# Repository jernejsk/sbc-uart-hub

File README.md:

# SBC UART hub (rev A)

A 16-channel 3.3 V debug-UART adapter for the SBC farm, connected over one USB cable.

```
USB-C ── USBLC6 ── USB2514B hub ──┬── FT4232HL #1  CH01-04 (top row, left)
                                  ├── FT4232HL #2  CH05-08 (top row, right)
                                  ├── FT4232HL #3  CH09-12 (bottom row, left)
                                  └── FT4232HL #4  CH13-16 (bottom row, right)
```

The datasheet with 3D renders, for design review, is at `docs/datasheet.html` (images in `docs/img/`).

Each channel works as follows:

- The FT TXD goes through a 74LVC125 buffer, then 220R, to the header. The buffer's /OE is that channel's DTR#.
- The connector RX comes in through 220R and the 74LVC125 (always enabled) to the FT RXD.
- The ESDA6V1-5SC6 clamps the connector pins to GND only. It has no VCC rail.
- A green LED lights while DTR is asserted, which means the port is open and TX is driven.

TX is Hi-Z whenever the port is closed. LVC parts have Ioff, so both TX and RX are also Hi-Z when the board is unpowered. As a result the DUT is never back-powered, and the cable carries no VCC.

## Connector (1x3 2.54 mm right-angle header, LCSC C492411)

| pin | signal | direction |
|-----|--------|-----------|
| 1 (square) | GND | |
| 2 | TX | adapter → DUT RX |
| 3 | RX | DUT TX → adapter |

Each header's plastic body is flush with the board edge, and its pins stick out about 6 mm past it. Pin 1 (GND, square pad) is on the right in the top row (CH01-08) and on the left in the bottom row (CH09-16). GND, TX and RX are printed next to every pin.

The project footprint (`gen/mkfp.py`, `hw/lib/sbcu.pretty`) numbers its pads the mirror of KiCad's stock right-angle header. That puts each signal where it was on the earlier JST-XH layout (commit 3d51c3360c3e), so that routing was kept; the header itself is symmetric. `gen/rework_headers.py` did the migration: it swapped the footprints, ripped only the connector stubs and locked the rest. It then had Freerouting finish the stubs. A fresh `build_pcb.py` + `route.py` run gives the same placement but a different autorouted result.

Cables are plain female-female Dupont jumper wires, one per signal, so any DUT header order works. Plugging one onto the wrong pin is harmless: there is no VCC pin, and both lines have 220R in series behind an LVC buffer.

The back silkscreen has a write-on box for each channel where you note the labgrid place name.

## Channel map

| CH | FT / EEPROM serial | interface | hub port (`uhubctl -p`) |
|----|-----|-----|-----|
| 01-04 | FT1 / SBCU-1 | 00-03 | 4 |
| 05-08 | FT2 / SBCU-2 | 00-03 | 3 |
| 09-12 | FT3 / SBCU-3 | 00-03 | 1 |
| 13-16 | FT4 / SBCU-4 | 00-03 | 2 |

The hub-port-to-FT order comes from the PCB layout: it keeps the four USB lanes from crossing.

## Design notes

- **Power:** USB bus powered. A TLV62569 buck makes 3.3 V. From the datasheets: each FT4232H draws 70 mA core (through its 1.8 V regulator) plus 30 mA typ / 60 mA max for the PHY, the hub about 100 mA, the LEDs about 1 mA each. That is about 0.55 A typical and 0.66 A worst case at 3.3 V, or 0.40 A typical and 0.49 A worst case from 5 V at 90 % buck efficiency. That sits just inside the 500 mA that a bus-powered hub may declare (hub 100 mA + 4 × 100 mA), so each FT's EEPROM must declare `max_power=100`. The hub straps are CFG_SEL=10 (default configuration, bus-powered override: individual port power switching, strap options enabled) and NON_REM=00 (all ports removable; the straps cannot mark all four ports non-removable, and it changes nothing for Linux).
- **Crystals:** 12 MHz (C9002, 20 pF CL) with 27 pF as FTDI recommends; 24 MHz (C15643, 20 pF CL) with 33 pF, per Microchip's C = 2·CL − C_stray. The previous 24 MHz part (C70590) was a 12 pF CL crystal, which would have wanted 18 pF.
- **Hard reset per FT (optional):** fit R14–R17 (0R, PRTPWRn → RESET#) and remove the matching RESET# 10k pull-ups. Then `uhubctl -a cycle -p N` resets that FT4232H. While a chip is held in reset its pins float high, so TX stays Hi-Z. As shipped these are DNP. The hub only samples BC_EN (on the PRTPWR pins) at reset, which is why they are not pulled up.
- **USB pairs:** 0.22 mm track / 0.15 mm gap on L1 over the In1 GND plane, on JLC04161H-7628 (7628 PP 0.2104 mm, Dk 4.4). JLC's own impedance solver (queried 2026-11-08) gives 93.0 Ω for a coated edge-coupled microstrip and 92.1 Ω for coplanar with the 0.3 mm GND pour. Both are inside USB 2.0's 90 Ω ±15 %. A 0.24/0.15 pair would land at 89–90 Ω. Both the hub and the FT number DM before DP counter-clockwise, so every pair needs a polarity swap. DP drops to B.Cu next to the FT for this (two vias).
- **Stackup:** 4 layers: F.Cu signal, In1 GND plane, In2 3V3 plane, B.Cu signal. Every GND/3V3 SMD pad gets its own via. All parts are on the top side. The headers are THT.

## Regenerating

Everything is scripted. You need KiCad 9 (PPA), Java 25 and Freerouting 2.5.0 (`~/research/sbc-uart/tools/`).

```
python3 gen/mkfp.py          # project footprint hw/lib/sbcu.pretty (edge-mounted right-angle header)
python3 gen/design.py        # schematic  (hw/*.kicad_sch), then: kicad-cli sch erc
python3 gen/build_pcb.py     # netlist -> placement, USB pairs, planes, GND/3V3 fan-out
python3 gen/route.py 100     # Freerouting (~11 min) -> routed board; may leave a few open, check DRC
python3 gen/finish.py        # silkscreen, outer GND pours, cleanup, zone fill
python3 gen/fab.py --boards 5  # gerbers zip, BOM/CPL, PDF, renders, JLC stock check
```

The KiCad library has no 3D models for J1 (HRO TYPE-C-31-M-12) and L1. Models from LCSC/EasyEDA are in `hw/lib/3d/`, and `finish.py` assigns them.

`hw/build/` (not committed) holds the netlist, the DSN/SES files and `routed-1.kicad_pcb` (the raw autorouter output). You can re-run `finish.py` on a copy of it.

## Ordering (JLCPCB)

- PCB: 4 layers, 1.6 mm, impedance control with stackup **JLC04161H-7628**. Upload `fab/sbc-uart-hub-gerbers.zip`.
- PCBA: top side, with `fab/bom_jlc.csv` and `fab/cpl_jlc.csv`. The headers are through-hole and need THT assembly.
- CPL rotations and offsets are measured, not guessed. `gen/jlc_rot.py` fits each KiCad footprint onto JLC's own EasyEDA footprint for that LCSC part. It matches pads by number, LEDs by the cathode pin name, and rejects any rotation that puts the part body on the wrong side (needed for the headers, whose pad numbering is mirrored against JLC's, and in general for anything with a symmetric pad row). The result goes to `gen/jlc_rot.json`, which `fab.py` applies. Checked on 2026-11-08: every pad lands within 0.21 mm of JLC's pad, pin 1 or the cathode is in place on all 286 placements, and the header bodies and the USB-C point off the board edge.
  - The same KiCad footprint can need different rotations: the three SOT-23-6 parts need 270, 270 and 180.
  - JLC centres the headers on the middle pin, and the USB-C 1.6 mm off the KiCad origin.
  - It still assumes JLC places parts at the EasyEDA footprint origin. Glance at the USB-C and the headers in the PCBA preview.
- To refetch the footprints: `easyeda2kicad --footprint --symbol --lcsc_id=C.. --output <dir>/C../lib` per part (the API rate-limits, so pace the requests). Then run `python3 gen/jlc_rot.py <dir>`.
- Cost (5 boards, Nov 2026): about $59 of parts per board. The four FT4232HL are $50 of that.

## Bring-up

1. `lsusb` shows the hub and 4× `0403:6011`.
2. Run `host/program-eeproms.sh <hub-sysfs-name>`, then replug. Check the serials `SBCU-1..4`.
3. Install `host/70-sbc-uart-hub.rules`. You get `/dev/sbcu/ch01..16`.
4. Loopback test: wire CH01 TX to CH02 RX.
   - With the port closed, TX must read Hi-Z (100k to GND gives 0 V).
   - With the port open, data must pass at 115200 and 1.5 Mbaud.
5. Back-power test: with the DUT off and the port closed, the DUT 3.3 V rail stays at 0 V. Repeat with the USB cable unplugged.
6. Labgrid: see `host/labgrid-exporter.yaml`. TX is only gated while nobody holds the port open. Check that your ser2net setup opens the tty only while a client is connected, so DTR drops in between.

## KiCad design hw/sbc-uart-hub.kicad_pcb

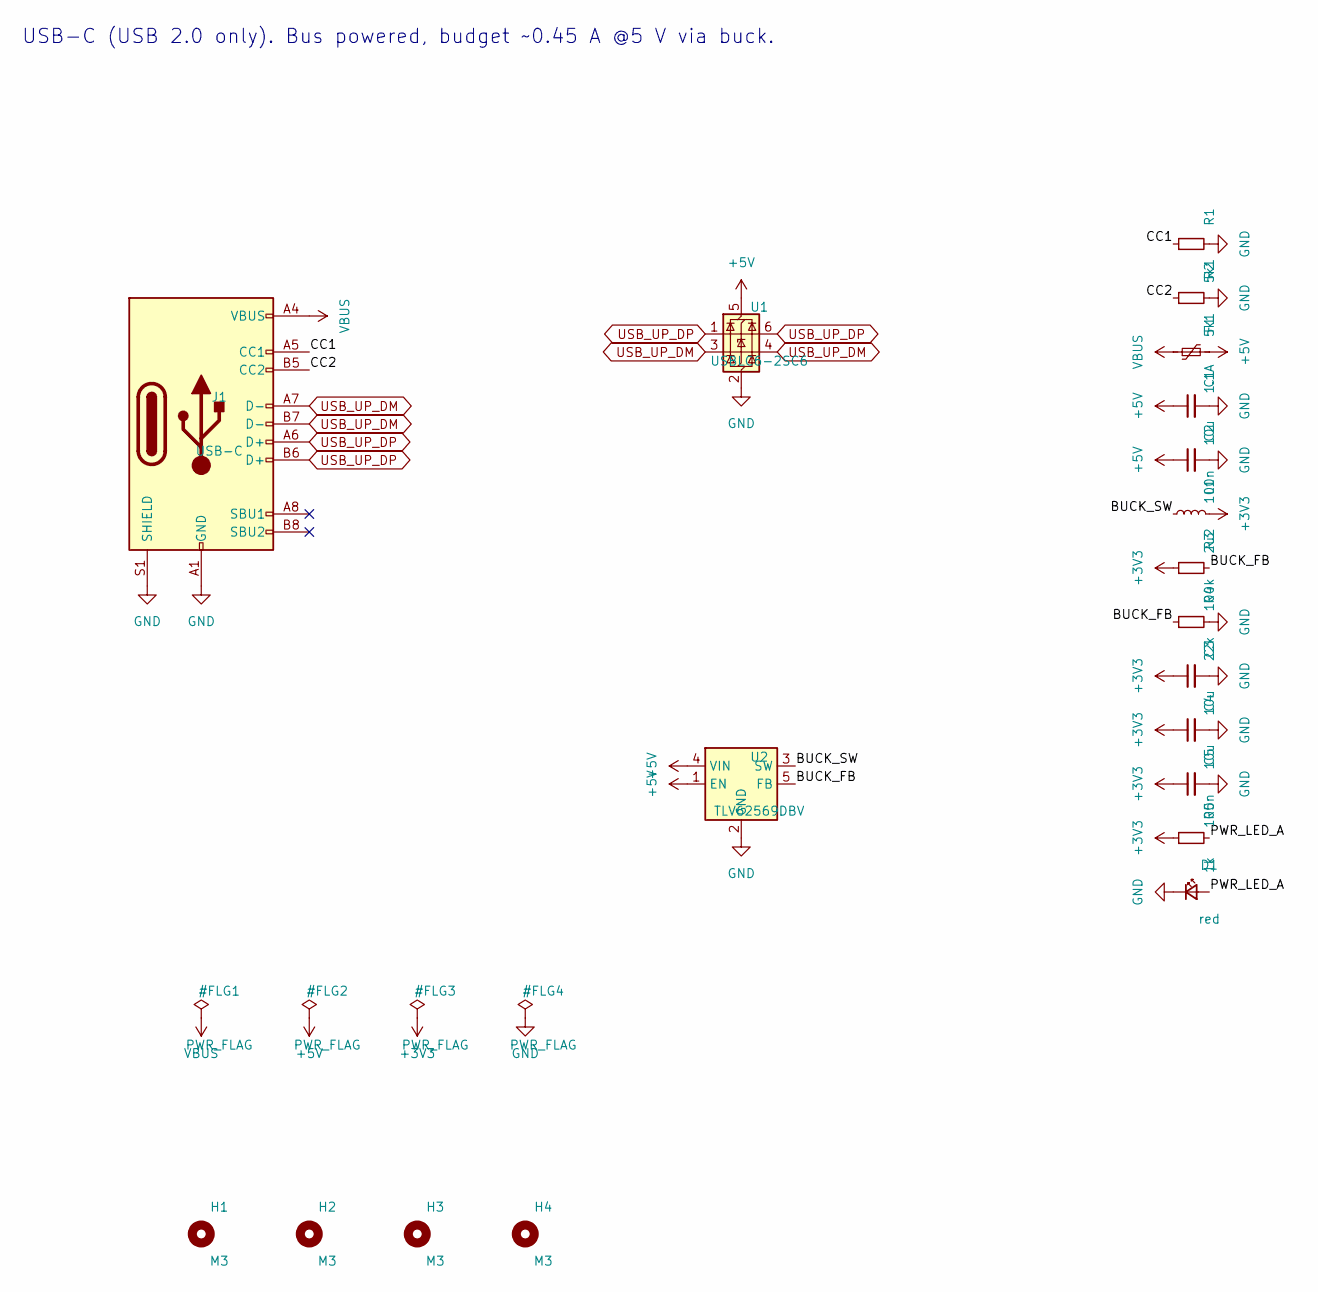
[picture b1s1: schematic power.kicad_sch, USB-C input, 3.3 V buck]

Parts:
C1, C3, C4: 10u; C_0805_2012Metric; MPN CL21A106KAYNNNE; LCSC C15850
C2, C5: 100n; C_0402_1005Metric; MPN CL05B104KO5NNNC; LCSC C1525
D1: red; LED_0603_1608Metric; MPN KT-0603R; LCSC C2286
F1: 1.1A; Fuse_1206_3216Metric; MPN SMD1206P110TF; LCSC C20801
H1, H2, H3, H4: M3; MountingHole_3.2mm_M3
J1: USB-C; USB_C_Receptacle_HRO_TYPE-C-31-M-12; MPN TYPE-C-31-M-12; LCSC C165948
L1: 2u2; L_Taiyo-Yuden_NR-40xx; MPN SWPA4020S2R2MT; LCSC C83423
R1, R2: 5k1; R_0402_1005Metric; MPN 0402WGF5101TCE; LCSC C25905
R3: 100k; R_0402_1005Metric; MPN 0402WGF1003TCE; LCSC C25741
R4: 22k; R_0402_1005Metric; MPN 0402WGF2202TCE; LCSC C25768
R5: 1k; R_0402_1005Metric; MPN 0402WGF1001TCE; LCSC C11702
U1: USBLC6-2SC6; SOT-23-6; MPN USBLC6-2SC6; LCSC C7519
U2: TLV62569DBV; SOT-23-5; MPN TLV62569DBVR; LCSC C141836

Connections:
+3V3: C3.1, C4.1, C5.1, L1.2, R3.1, R5.1; also elsewhere on the board
+5V: C1.1, C2.1, F1.2, U1.5 (VBUS), U2.1 (EN), U2.4 (VIN); also elsewhere on the board
/Power/BUCK_FB: R3.2, R4.1, U2.5 (FB)
/Power/BUCK_SW: L1.1, U2.3 (SW)
/Power/CC1: J1.A5 (CC1), R1.1
/Power/CC2: J1.B5 (CC2), R2.1
/Power/PWR_LED_A: D1.2 (A), R5.2
GND: C1.2, C2.2, C3.2, C4.2, C5.2, D1.1 (K), J1.A1 (GND), J1.A12 (GND), J1.B1 (GND), J1.B12 (GND), J1.S1 (SHIELD), R1.2, R2.2, R4.2, U1.2 (GND), U2.2 (GND); also elsewhere on the board
USB_UP_DM: J1.A7 (D-), J1.B7 (D-), U1.3 (I/O2), U1.4 (I/O2); also elsewhere on the board
USB_UP_DP: J1.A6 (D+), J1.B6 (D+), U1.1 (I/O1), U1.6 (I/O1); also elsewhere on the board
VBUS: F1.1, J1.A4 (VBUS), J1.A9 (VBUS), J1.B4 (VBUS), J1.B9 (VBUS)

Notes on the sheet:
USB-C (USB 2.0 only). Bus powered, budget ~0.45 A @5 V via buck.

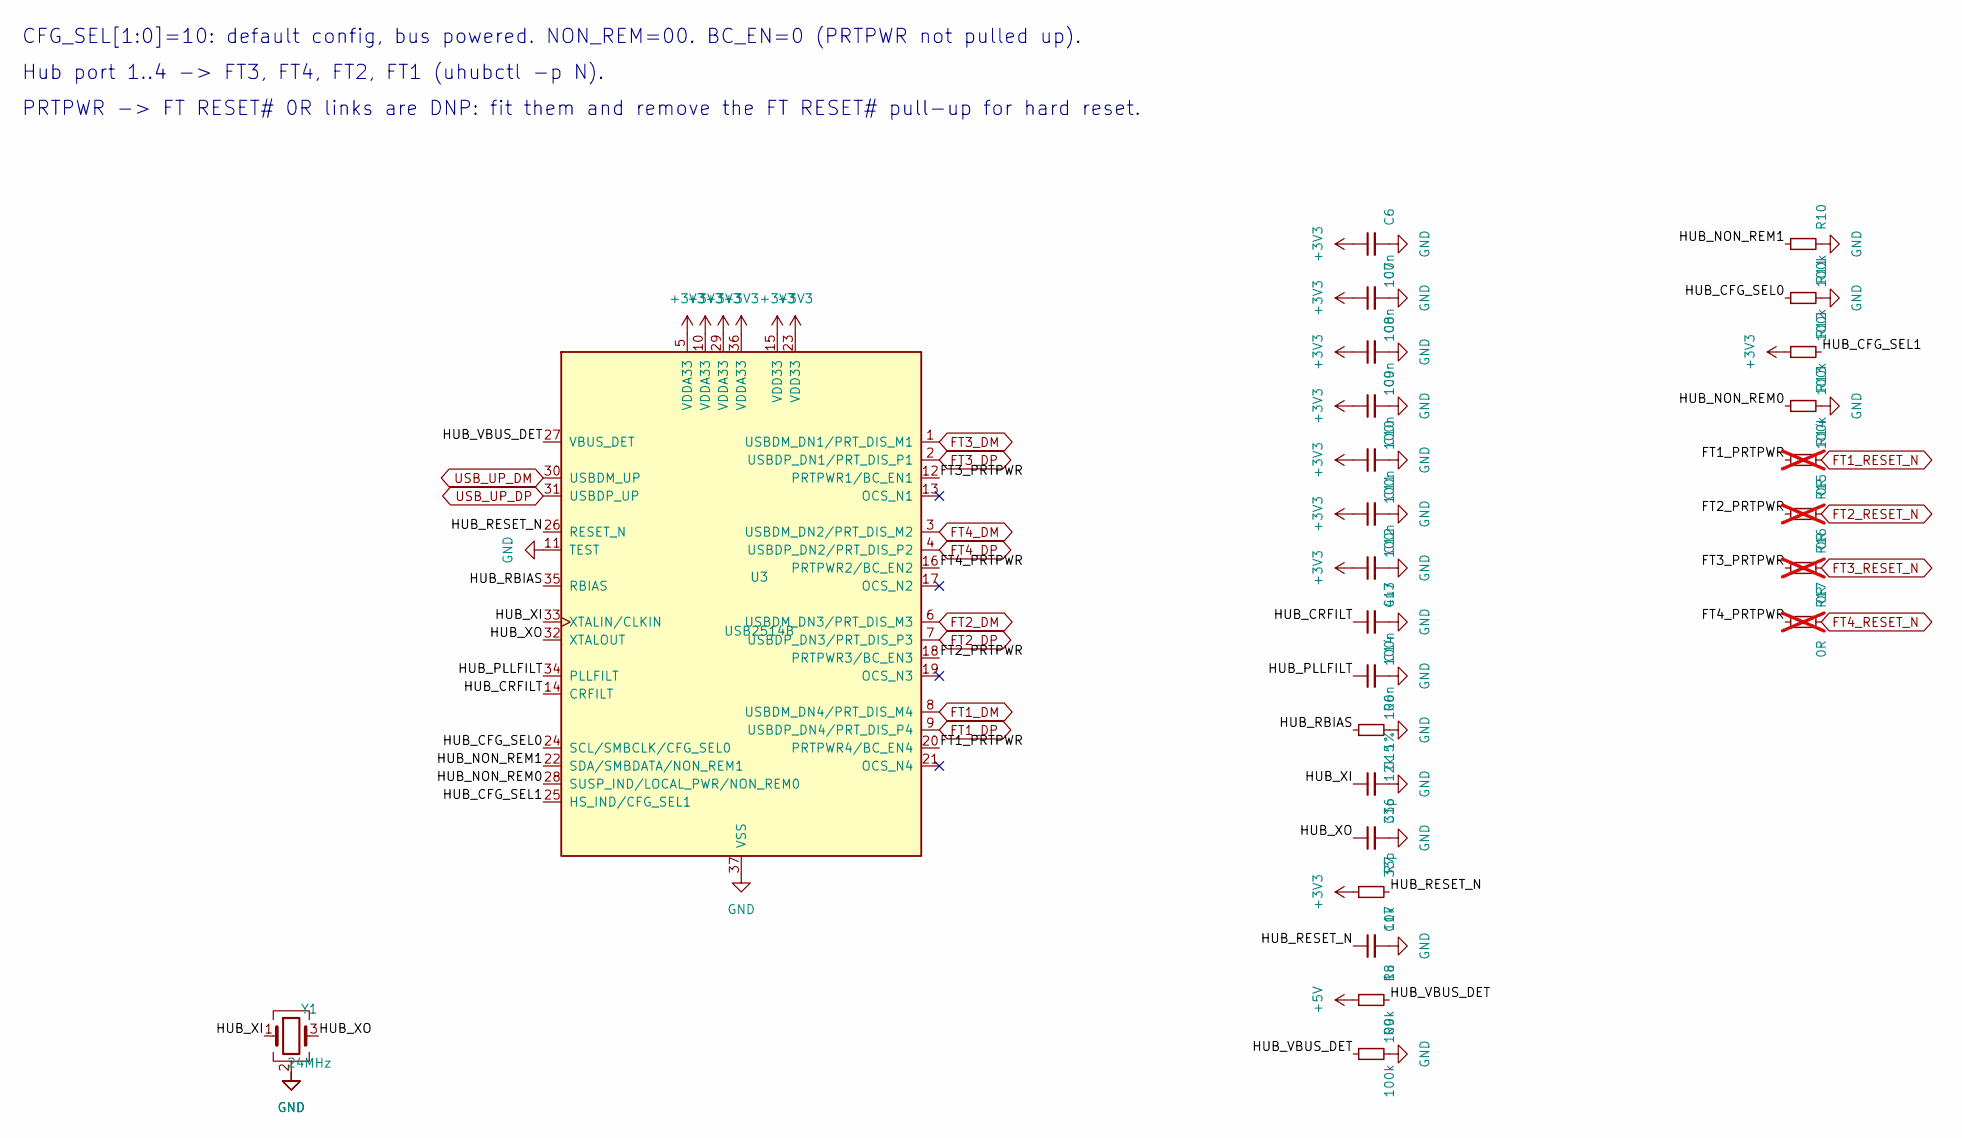
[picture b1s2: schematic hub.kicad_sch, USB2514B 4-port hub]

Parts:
C6, C7, C8, C9, C10, C11, C13, C14: 100n; C_0402_1005Metric; MPN CL05B104KO5NNNC; LCSC C1525
C12: 4u7; C_0805_2012Metric; MPN CL21A475KAQNNNE; LCSC C1779
C15, C16: 33p; C_0402_1005Metric; MPN 0402CG330J500NT; LCSC C1562
C17: 1u; C_0402_1005Metric; MPN CL05A105KA5NQNC; LCSC C52923
R6: 12k 1%; R_0402_1005Metric; MPN 0402WGF1202TCE; LCSC C25752
R7: 10k; R_0402_1005Metric; MPN 0402WGF1002TCE; LCSC C25744
R8, R9, R10, R11, R12, R13: 100k; R_0402_1005Metric; MPN 0402WGF1003TCE; LCSC C25741
R14, R15, R16, R17: 0R; R_0402_1005Metric; MPN 0402WGF0000TCE; LCSC C17168; not fitted
U3: USB2514B; QFN-36-1EP_6x6mm_P0.5mm_EP3.7x3.7mm; MPN USB2514B-AEZC-TR; LCSC C16251
Y1: 24MHz; Crystal_SMD_3225-4Pin_3.2x2.5mm; MPN X322524MSB4SI; LCSC C15643

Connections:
+3V3: C6.1, C7.1, C8.1, C9.1, C10.1, C11.1, C12.1, R7.1, R12.1, U3.5 (VDDA33), U3.10 (VDDA33), U3.15 (VDD33), U3.23 (VDD33), U3.29 (VDDA33), U3.36 (VDDA33); also elsewhere on the board
+5V: R8.1; also elsewhere on the board
/Hub/FT1_PRTPWR: R14.1, U3.20 (PRTPWR4/BC_EN4)
/Hub/FT2_PRTPWR: R15.1, U3.18 (PRTPWR3/BC_EN3)
/Hub/FT3_PRTPWR: R16.1, U3.12 (PRTPWR1/BC_EN1)
/Hub/FT4_PRTPWR: R17.1, U3.16 (PRTPWR2/BC_EN2)
/Hub/HUB_CFG_SEL0: R11.1, U3.24 (SCL/SMBCLK/CFG_SEL0)
/Hub/HUB_CFG_SEL1: R12.2, U3.25 (HS_IND/CFG_SEL1)
/Hub/HUB_CRFILT: C13.1, U3.14 (CRFILT)
/Hub/HUB_NON_REM0: R13.1, U3.28 (SUSP_IND/LOCAL_PWR/NON_REM0)
/Hub/HUB_NON_REM1: R10.1, U3.22 (SDA/SMBDATA/NON_REM1)
/Hub/HUB_PLLFILT: C14.1, U3.34 (PLLFILT)
/Hub/HUB_RBIAS: R6.1, U3.35 (RBIAS)
/Hub/HUB_RESET_N: C17.1, R7.2, U3.26 (RESET_N)
/Hub/HUB_VBUS_DET: R8.2, R9.1, U3.27 (VBUS_DET)
/Hub/HUB_XI: C15.1, U3.33 (XTALIN/CLKIN), Y1.1
/Hub/HUB_XO: C16.1, U3.32 (XTALOUT), Y1.3
FT1_DM: U3.8 (USBDM_DN4/PRT_DIS_M4); also elsewhere on the board
FT1_DP: U3.9 (USBDP_DN4/PRT_DIS_P4); also elsewhere on the board
FT1_RESET_N: R14.2; also elsewhere on the board
FT2_DM: U3.6 (USBDM_DN3/PRT_DIS_M3); also elsewhere on the board
FT2_DP: U3.7 (USBDP_DN3/PRT_DIS_P3); also elsewhere on the board
FT2_RESET_N: R15.2; also elsewhere on the board
FT3_DM: U3.1 (USBDM_DN1/PRT_DIS_M1); also elsewhere on the board
FT3_DP: U3.2 (USBDP_DN1/PRT_DIS_P1); also elsewhere on the board
FT3_RESET_N: R16.2; also elsewhere on the board
FT4_DM: U3.3 (USBDM_DN2/PRT_DIS_M2); also elsewhere on the board
FT4_DP: U3.4 (USBDP_DN2/PRT_DIS_P2); also elsewhere on the board
FT4_RESET_N: R17.2; also elsewhere on the board
GND: C6.2, C7.2, C8.2, C9.2, C10.2, C11.2, C12.2, C13.2, C14.2, C15.2, C16.2, C17.2, R6.2, R9.2, R10.2, R11.2, R13.2, U3.11 (TEST), U3.37 (VSS), Y1.2 (G), Y1.4 (G); also elsewhere on the board
USB_UP_DM: U3.30 (USBDM_UP); also elsewhere on the board
USB_UP_DP: U3.31 (USBDP_UP); also elsewhere on the board

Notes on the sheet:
CFG_SEL[1:0]=10: default config, bus powered. NON_REM=00. BC_EN=0 (PRTPWR not pulled up).
Hub port 1..4 -> FT3, FT4, FT2, FT1 (uhubctl -p N).
PRTPWR -> FT RESET# 0R links are DNP: fit them and remove the FT RESET# pull-up for hard reset.

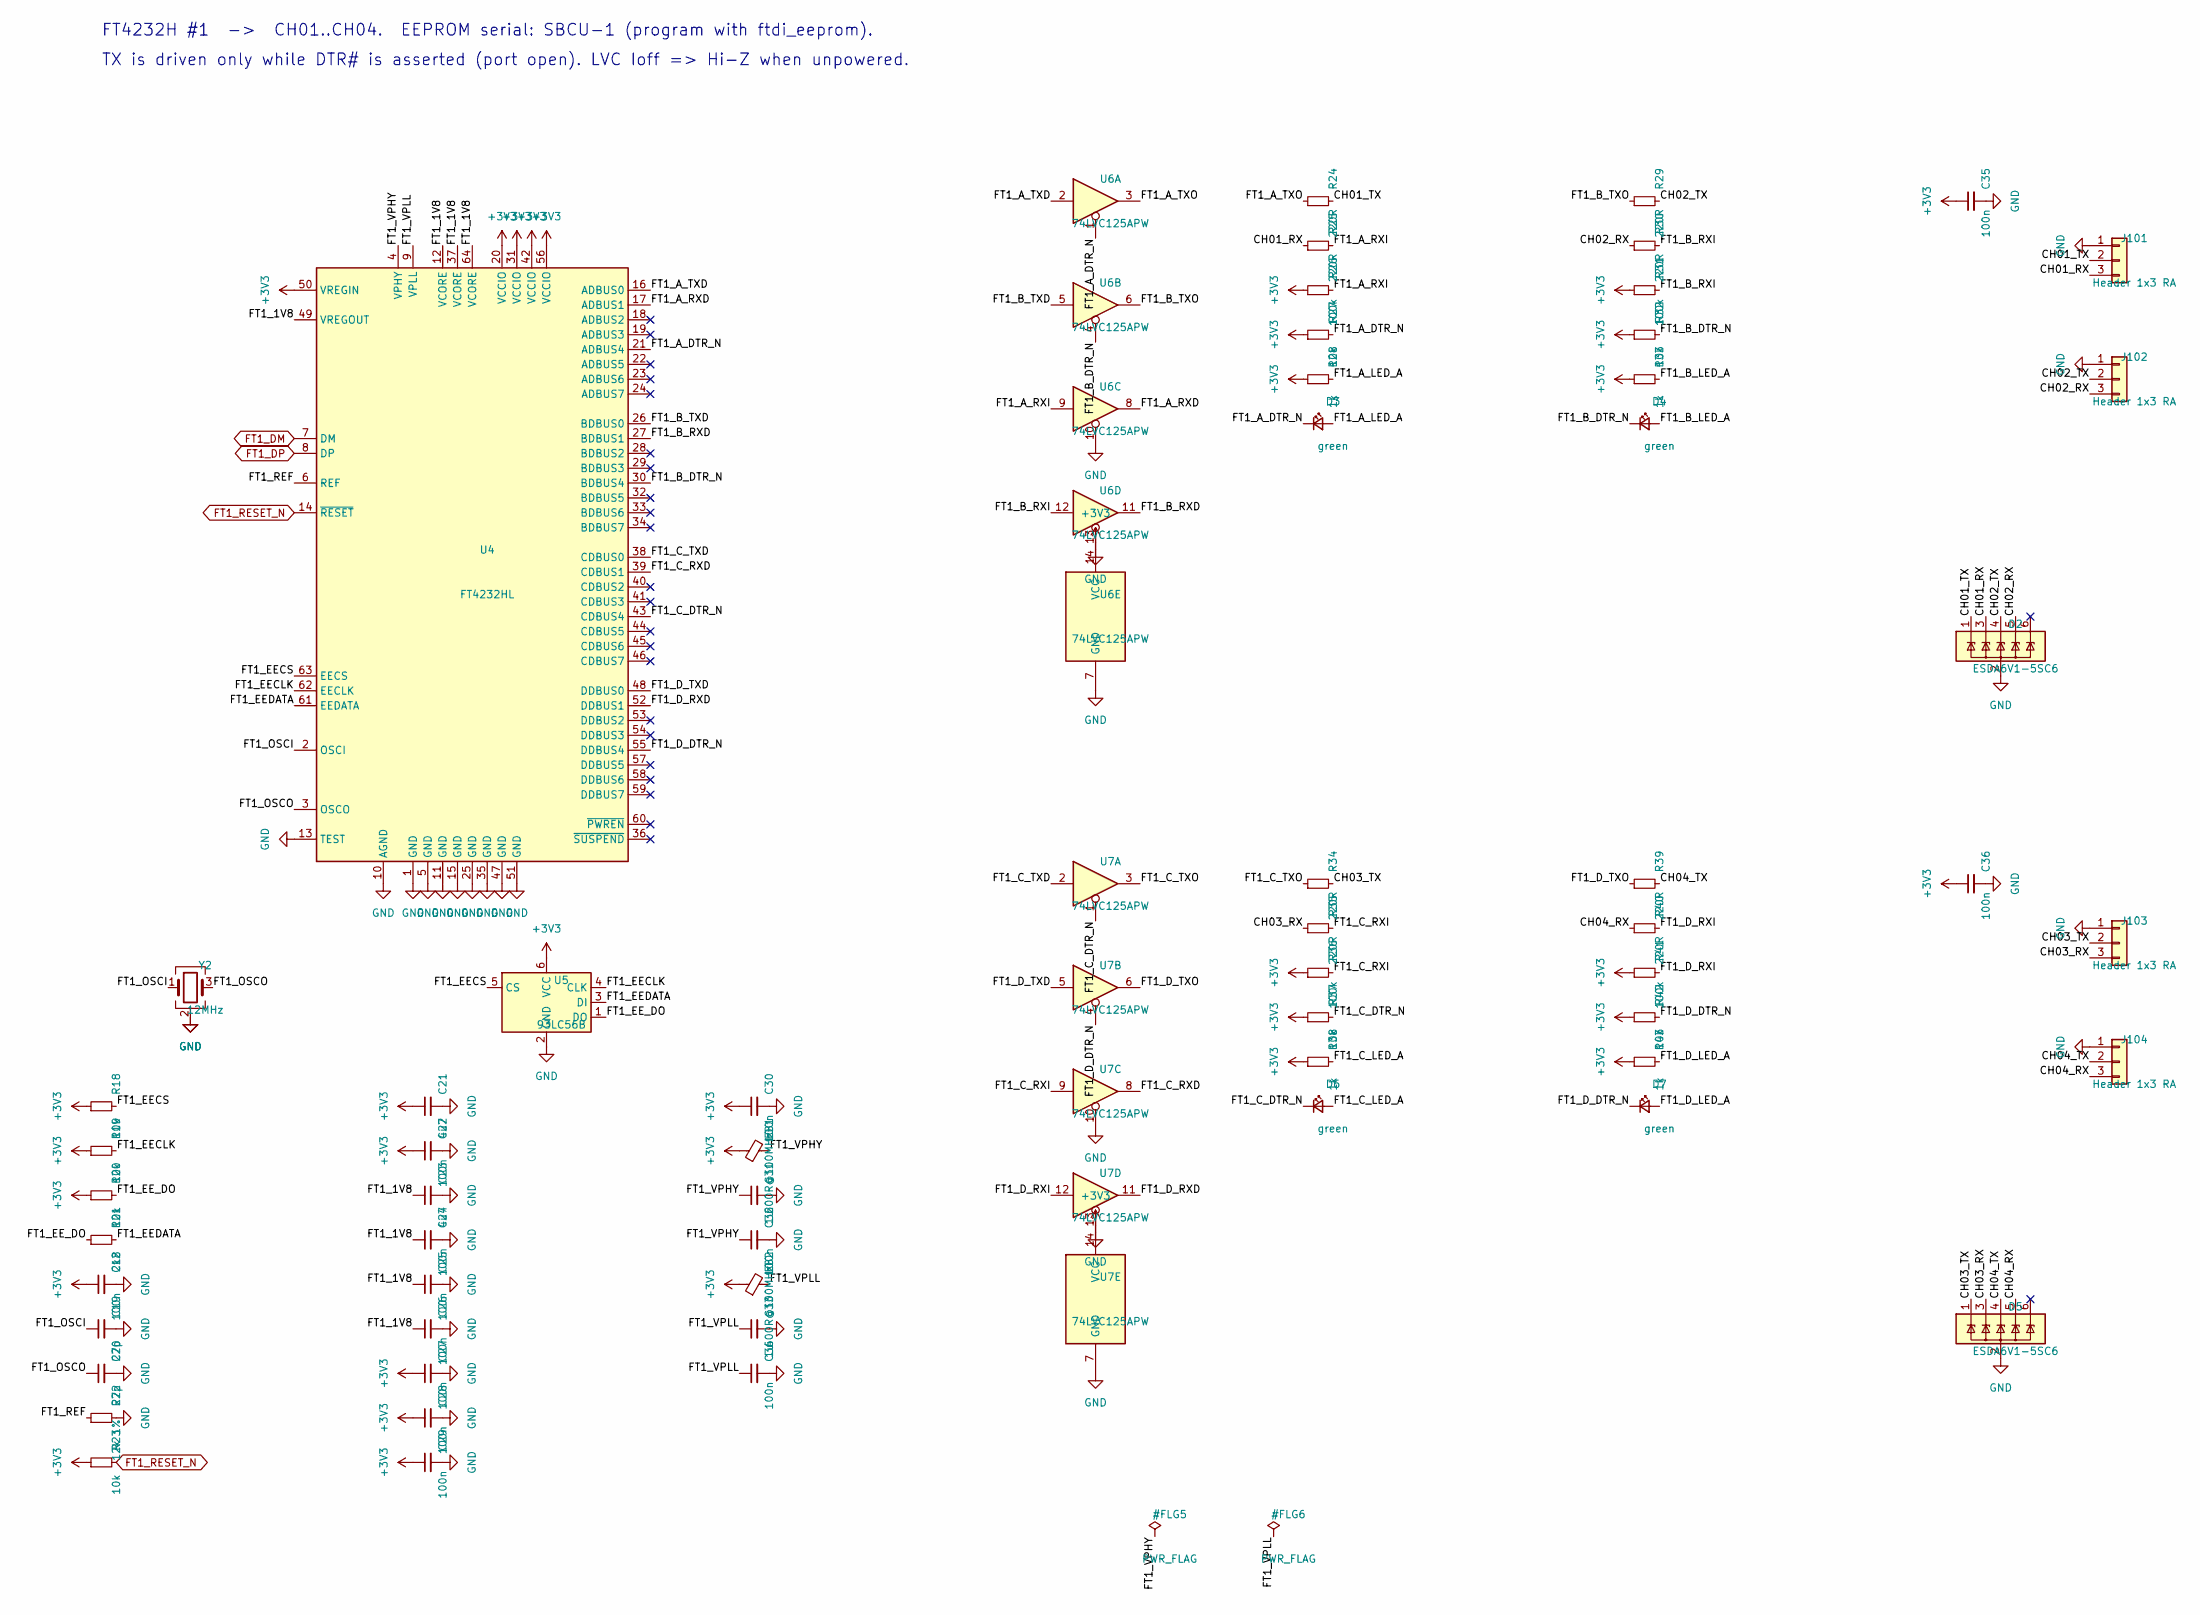
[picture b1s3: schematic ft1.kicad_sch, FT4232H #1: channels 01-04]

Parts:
C18, C22, C24, C25, C26, C27, C28, C29, C30, C32, C34, C35, C36: 100n; C_0402_1005Metric; MPN CL05B104KO5NNNC; LCSC C1525
C19, C20: 27p; C_0402_1005Metric; MPN 0402CG270J500NT; LCSC C1557
C21, C23: 4u7; C_0805_2012Metric; MPN CL21A475KAQNNNE; LCSC C1779
C31, C33: 1u; C_0402_1005Metric; MPN CL05A105KA5NQNC; LCSC C52923
D2, D5: ESDA6V1-5SC6; SOT-23-6; MPN ESDA6V1-5SC6; LCSC C2827672
D3, D4, D6, D7: green; LED_0603_1608Metric; MPN KT-0603G; LCSC C12624
FB1, FB2: 600R@100MHz; L_0603_1608Metric; MPN GZ1608D601TF; LCSC C1002
J101, J102, J103, J104: Header 1x3 RA; PinHeader_1x03_P2.54mm_Horizontal_Edge; MPN PZ254R-11-03P; LCSC C492411
R18, R19, R20, R23, R27, R32, R37, R42: 10k; R_0402_1005Metric; MPN 0402WGF1002TCE; LCSC C25744
R21: 2k2; R_0402_1005Metric; MPN 0402WGF2201TCE; LCSC C25879
R22: 12k 1%; R_0402_1005Metric; MPN 0402WGF1202TCE; LCSC C25752
R24, R25, R29, R30, R34, R35, R39, R40: 220R; R_0402_1005Metric; MPN 0402WGF2200TCE; LCSC C25091
R26, R31, R36, R41: 100k; R_0402_1005Metric; MPN 0402WGF1003TCE; LCSC C25741
R28, R33, R38, R43: 1k; R_0402_1005Metric; MPN 0402WGF1001TCE; LCSC C11702
U4: FT4232HL; LQFP-64_10x10mm_P0.5mm; MPN FT4232HL-REEL; LCSC C56742
U5: 93LC56B; SOT-23-6; MPN 93LC56BT-I/OT; LCSC C190271
U6, U7: 74LVC125APW; TSSOP-14_4.4x5mm_P0.65mm; MPN 74LVC125APW,118; LCSC C6059
Y2: 12MHz; Crystal_SMD_3225-4Pin_3.2x2.5mm; MPN X322512MSB4SI; LCSC C9002

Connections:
+3V3: C18.1, C21.1, C22.1, C27.1, C28.1, C29.1, C30.1, C35.1, C36.1, FB1.1, FB2.1, R18.1, R19.1, R20.1, R23.1, R26.1, R27.1, R28.1, R31.1, R32.1, R33.1, R36.1, R37.1, R38.1, R41.1, R42.1, R43.1, U4.20 (VCCIO), U4.31 (VCCIO), U4.42 (VCCIO), U4.50 (VREGIN), U4.56 (VCCIO), U5.6 (VCC), U6.14 (VCC), U7.14 (VCC); also elsewhere on the board
/FT1/CH01_RX: D2.3 (IO2), J101.3, R25.1
/FT1/CH01_TX: D2.1 (IO1), J101.2, R24.2
/FT1/CH02_RX: D2.5 (IO4), J102.3, R30.1
/FT1/CH02_TX: D2.4 (IO3), J102.2, R29.2
/FT1/CH03_RX: D5.3 (IO2), J103.3, R35.1
/FT1/CH03_TX: D5.1 (IO1), J103.2, R34.2
/FT1/CH04_RX: D5.5 (IO4), J104.3, R40.1
/FT1/CH04_TX: D5.4 (IO3), J104.2, R39.2
/FT1/FT1_1V8: C23.1, C24.1, C25.1, C26.1, U4.12 (VCORE), U4.37 (VCORE), U4.49 (VREGOUT), U4.64 (VCORE)
/FT1/FT1_A_DTR_N: D3.1 (K), R27.2, U4.21 (ADBUS4), U6.1
/FT1/FT1_A_LED_A: D3.2 (A), R28.2
/FT1/FT1_A_RXD: U4.17 (ADBUS1), U6.8
/FT1/FT1_A_RXI: R25.2, R26.2, U6.9
/FT1/FT1_A_TXD: U4.16 (ADBUS0), U6.2
/FT1/FT1_A_TXO: R24.1, U6.3
/FT1/FT1_B_DTR_N: D4.1 (K), R32.2, U4.30 (BDBUS4), U6.4
/FT1/FT1_B_LED_A: D4.2 (A), R33.2
/FT1/FT1_B_RXD: U4.27 (BDBUS1), U6.11
/FT1/FT1_B_RXI: R30.2, R31.2, U6.12
/FT1/FT1_B_TXD: U4.26 (BDBUS0), U6.5
/FT1/FT1_B_TXO: R29.1, U6.6
/FT1/FT1_C_DTR_N: D6.1 (K), R37.2, U4.43 (CDBUS4), U7.1
/FT1/FT1_C_LED_A: D6.2 (A), R38.2
/FT1/FT1_C_RXD: U4.39 (CDBUS1), U7.8
/FT1/FT1_C_RXI: R35.2, R36.2, U7.9
/FT1/FT1_C_TXD: U4.38 (CDBUS0), U7.2
/FT1/FT1_C_TXO: R34.1, U7.3
/FT1/FT1_D_DTR_N: D7.1 (K), R42.2, U4.55 (DDBUS4), U7.4
/FT1/FT1_D_LED_A: D7.2 (A), R43.2
/FT1/FT1_D_RXD: U4.52 (DDBUS1), U7.11
/FT1/FT1_D_RXI: R40.2, R41.2, U7.12
/FT1/FT1_D_TXD: U4.48 (DDBUS0), U7.5
/FT1/FT1_D_TXO: R39.1, U7.6
/FT1/FT1_EECLK: R19.2, U4.62 (EECLK), U5.4 (CLK)
/FT1/FT1_EECS: R18.2, U4.63 (EECS), U5.5 (CS)
/FT1/FT1_EEDATA: R21.2, U4.61 (EEDATA), U5.3 (DI)
/FT1/FT1_EE_DO: R20.2, R21.1, U5.1 (DO)
/FT1/FT1_OSCI: C19.1, U4.2 (OSCI), Y2.1
/FT1/FT1_OSCO: C20.1, U4.3 (OSCO), Y2.3
/FT1/FT1_REF: R22.1, U4.6 (REF)
/FT1/FT1_VPHY: C31.1, C32.1, FB1.2, U4.4 (VPHY)
/FT1/FT1_VPLL: C33.1, C34.1, FB2.2, U4.9 (VPLL)
FT1_DM: U4.7 (DM); also elsewhere on the board
FT1_DP: U4.8 (DP); also elsewhere on the board
FT1_RESET_N: R23.2, U4.14 (~RESET); also elsewhere on the board
GND: C18.2, C19.2, C20.2, C21.2, C22.2, C23.2, C24.2, C25.2, C26.2, C27.2, C28.2, C29.2, C30.2, C31.2, C32.2, C33.2, C34.2, C35.2, C36.2, D2.2 (GND), D5.2 (GND), J101.1, J102.1, J103.1, J104.1, R22.2, U4.1 (GND), U4.5 (GND), U4.10 (AGND), U4.11 (GND), U4.13 (TEST), U4.15 (GND), U4.25 (GND), U4.35 (GND), U4.47 (GND), U4.51 (GND), U5.2 (GND), U6.7 (GND), U6.10, U6.13, U7.7 (GND), U7.10, U7.13, Y2.2 (G), Y2.4 (G); also elsewhere on the board

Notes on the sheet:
FT4232H #1 -> CH01..CH04. EEPROM serial: SBCU-1 (program with ftdi_eeprom).
TX is driven only while DTR# is asserted (port open). LVC Ioff => Hi-Z when unpowered.

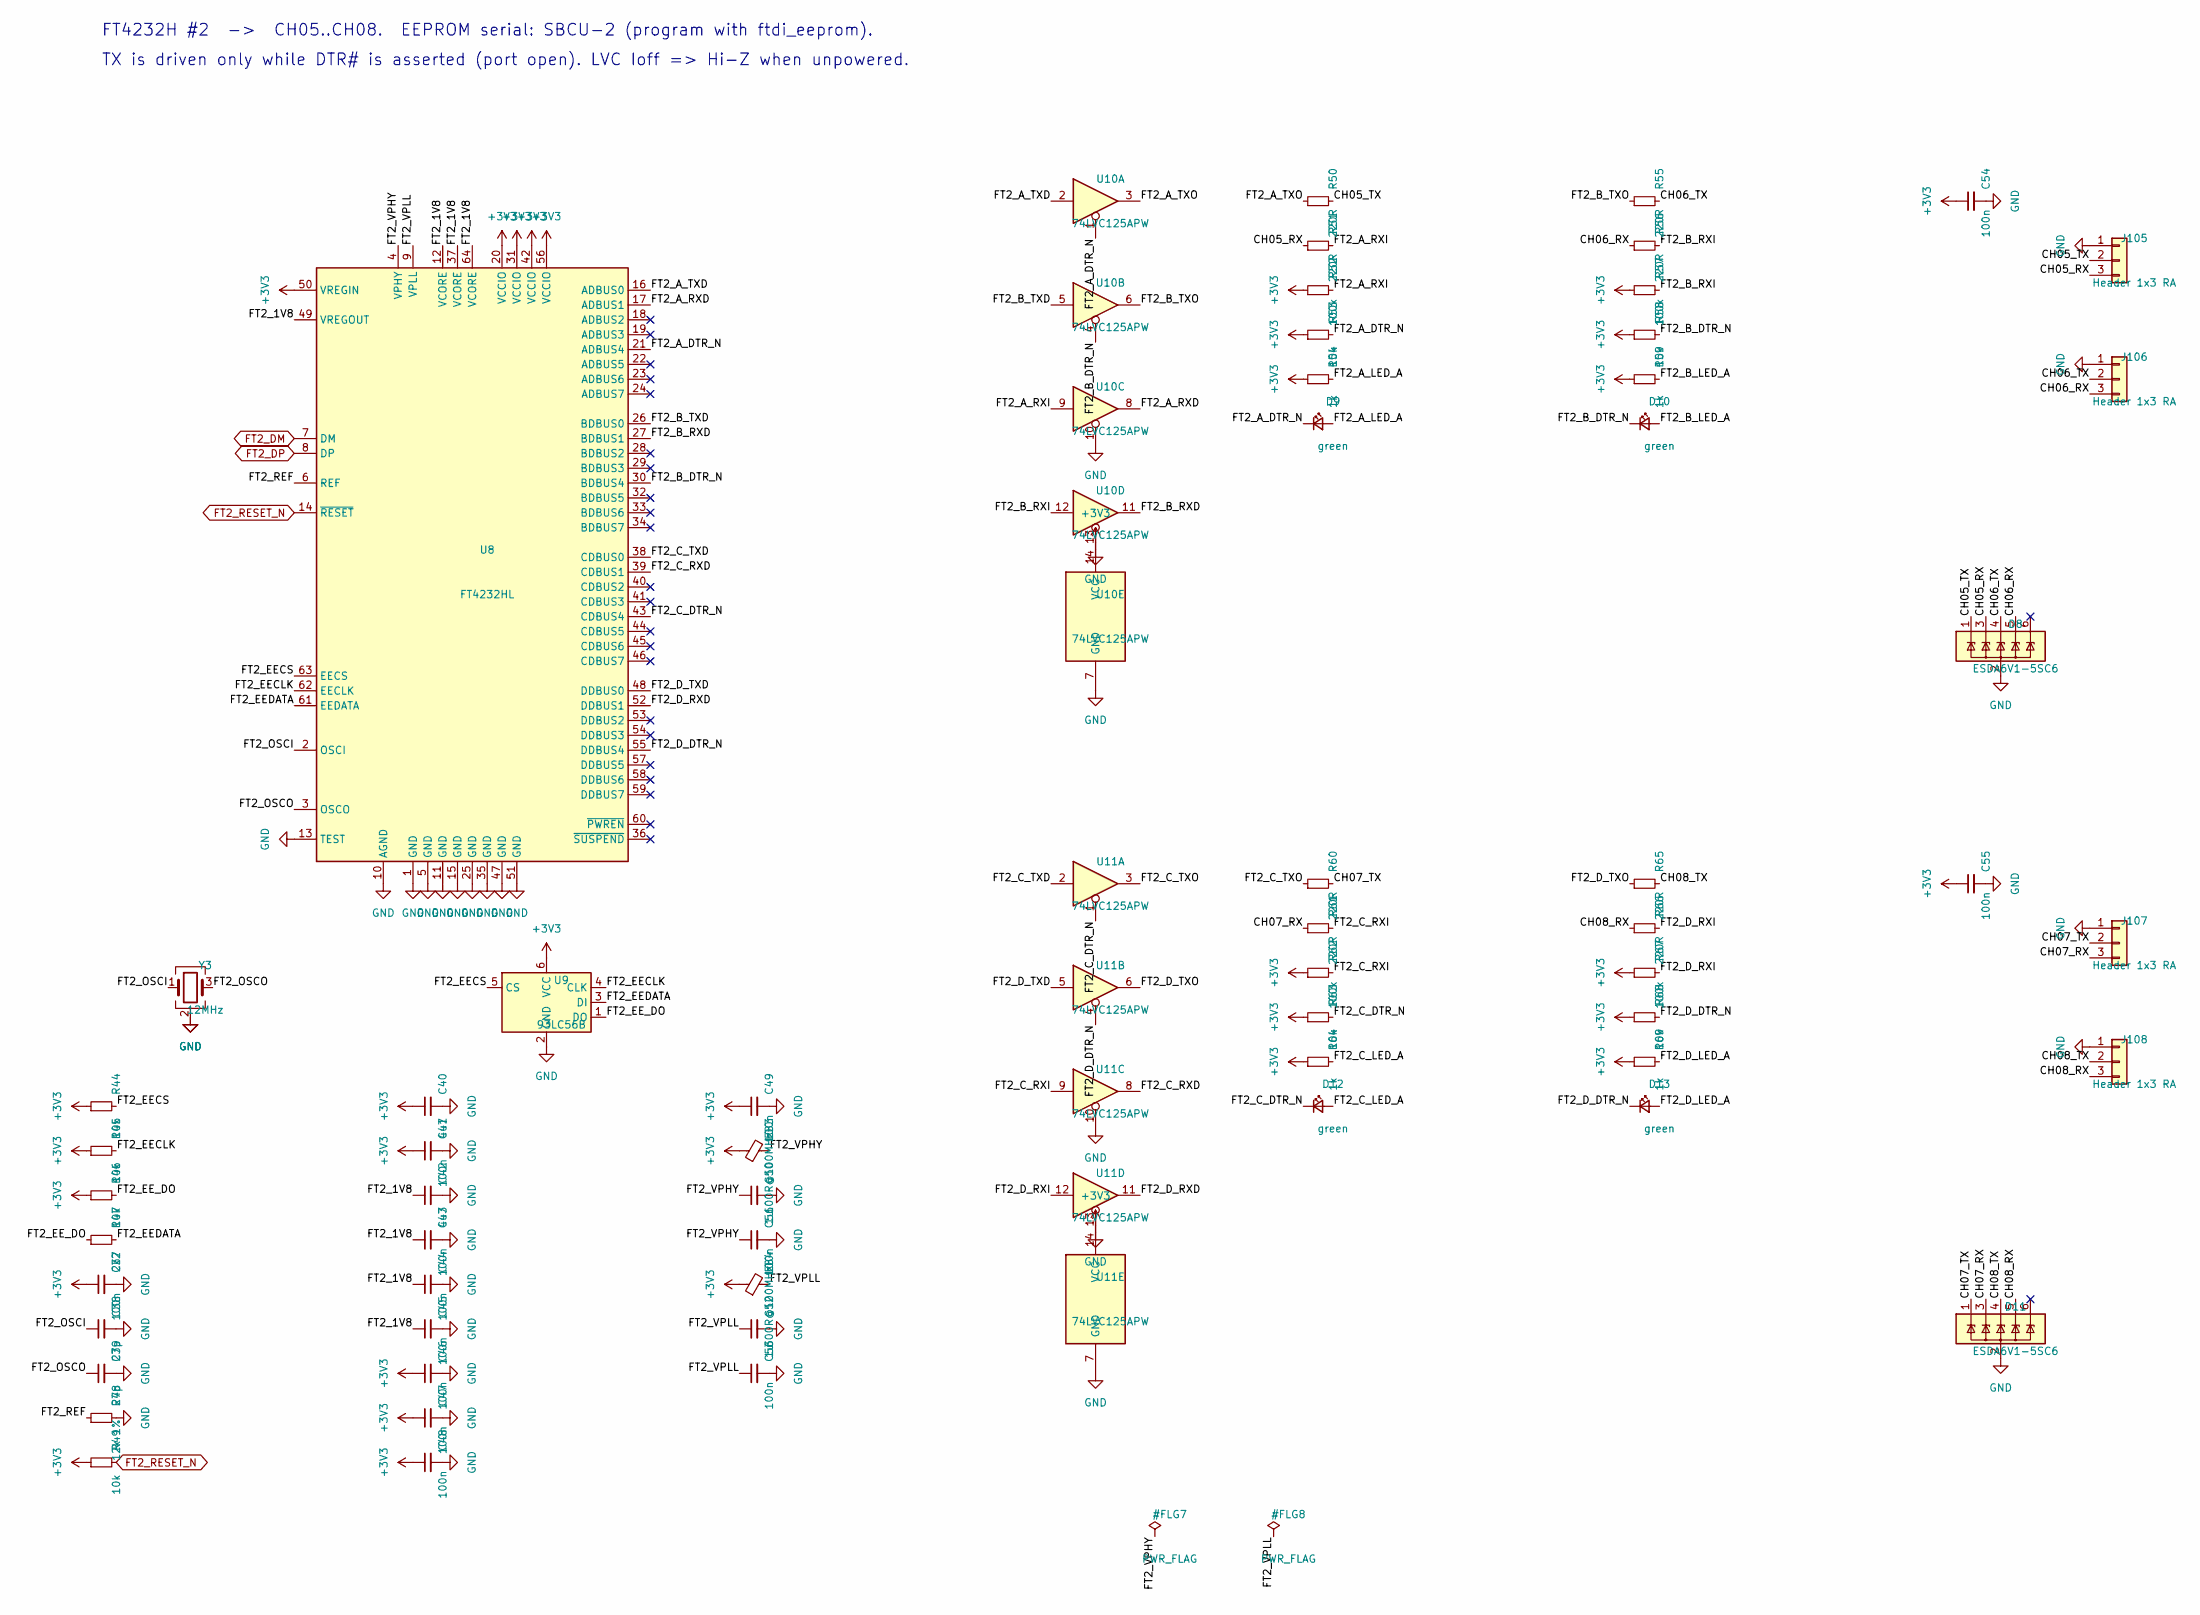
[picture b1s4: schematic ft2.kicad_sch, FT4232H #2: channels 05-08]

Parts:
C37, C41, C43, C44, C45, C46, C47, C48, C49, C51, C53, C54, C55: 100n; C_0402_1005Metric; MPN CL05B104KO5NNNC; LCSC C1525
C38, C39: 27p; C_0402_1005Metric; MPN 0402CG270J500NT; LCSC C1557
C40, C42: 4u7; C_0805_2012Metric; MPN CL21A475KAQNNNE; LCSC C1779
C50, C52: 1u; C_0402_1005Metric; MPN CL05A105KA5NQNC; LCSC C52923
D8, D11: ESDA6V1-5SC6; SOT-23-6; MPN ESDA6V1-5SC6; LCSC C2827672
D9, D10, D12, D13: green; LED_0603_1608Metric; MPN KT-0603G; LCSC C12624
FB3, FB4: 600R@100MHz; L_0603_1608Metric; MPN GZ1608D601TF; LCSC C1002
J105, J106, J107, J108: Header 1x3 RA; PinHeader_1x03_P2.54mm_Horizontal_Edge; MPN PZ254R-11-03P; LCSC C492411
R44, R45, R46, R49, R53, R58, R63, R68: 10k; R_0402_1005Metric; MPN 0402WGF1002TCE; LCSC C25744
R47: 2k2; R_0402_1005Metric; MPN 0402WGF2201TCE; LCSC C25879
R48: 12k 1%; R_0402_1005Metric; MPN 0402WGF1202TCE; LCSC C25752
R50, R51, R55, R56, R60, R61, R65, R66: 220R; R_0402_1005Metric; MPN 0402WGF2200TCE; LCSC C25091
R52, R57, R62, R67: 100k; R_0402_1005Metric; MPN 0402WGF1003TCE; LCSC C25741
R54, R59, R64, R69: 1k; R_0402_1005Metric; MPN 0402WGF1001TCE; LCSC C11702
U8: FT4232HL; LQFP-64_10x10mm_P0.5mm; MPN FT4232HL-REEL; LCSC C56742
U9: 93LC56B; SOT-23-6; MPN 93LC56BT-I/OT; LCSC C190271
U10, U11: 74LVC125APW; TSSOP-14_4.4x5mm_P0.65mm; MPN 74LVC125APW,118; LCSC C6059
Y3: 12MHz; Crystal_SMD_3225-4Pin_3.2x2.5mm; MPN X322512MSB4SI; LCSC C9002

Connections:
+3V3: C37.1, C40.1, C41.1, C46.1, C47.1, C48.1, C49.1, C54.1, C55.1, FB3.1, FB4.1, R44.1, R45.1, R46.1, R49.1, R52.1, R53.1, R54.1, R57.1, R58.1, R59.1, R62.1, R63.1, R64.1, R67.1, R68.1, R69.1, U8.20 (VCCIO), U8.31 (VCCIO), U8.42 (VCCIO), U8.50 (VREGIN), U8.56 (VCCIO), U9.6 (VCC), U10.14 (VCC), U11.14 (VCC); also elsewhere on the board
/FT2/CH05_RX: D8.3 (IO2), J105.3, R51.1
/FT2/CH05_TX: D8.1 (IO1), J105.2, R50.2
/FT2/CH06_RX: D8.5 (IO4), J106.3, R56.1
/FT2/CH06_TX: D8.4 (IO3), J106.2, R55.2
/FT2/CH07_RX: D11.3 (IO2), J107.3, R61.1
/FT2/CH07_TX: D11.1 (IO1), J107.2, R60.2
/FT2/CH08_RX: D11.5 (IO4), J108.3, R66.1
/FT2/CH08_TX: D11.4 (IO3), J108.2, R65.2
/FT2/FT2_1V8: C42.1, C43.1, C44.1, C45.1, U8.12 (VCORE), U8.37 (VCORE), U8.49 (VREGOUT), U8.64 (VCORE)
/FT2/FT2_A_DTR_N: D9.1 (K), R53.2, U8.21 (ADBUS4), U10.1
/FT2/FT2_A_LED_A: D9.2 (A), R54.2
/FT2/FT2_A_RXD: U8.17 (ADBUS1), U10.8
/FT2/FT2_A_RXI: R51.2, R52.2, U10.9
/FT2/FT2_A_TXD: U8.16 (ADBUS0), U10.2
/FT2/FT2_A_TXO: R50.1, U10.3
/FT2/FT2_B_DTR_N: D10.1 (K), R58.2, U8.30 (BDBUS4), U10.4
/FT2/FT2_B_LED_A: D10.2 (A), R59.2
/FT2/FT2_B_RXD: U8.27 (BDBUS1), U10.11
/FT2/FT2_B_RXI: R56.2, R57.2, U10.12
/FT2/FT2_B_TXD: U8.26 (BDBUS0), U10.5
/FT2/FT2_B_TXO: R55.1, U10.6
/FT2/FT2_C_DTR_N: D12.1 (K), R63.2, U8.43 (CDBUS4), U11.1
/FT2/FT2_C_LED_A: D12.2 (A), R64.2
/FT2/FT2_C_RXD: U8.39 (CDBUS1), U11.8
/FT2/FT2_C_RXI: R61.2, R62.2, U11.9
/FT2/FT2_C_TXD: U8.38 (CDBUS0), U11.2
/FT2/FT2_C_TXO: R60.1, U11.3
/FT2/FT2_D_DTR_N: D13.1 (K), R68.2, U8.55 (DDBUS4), U11.4
/FT2/FT2_D_LED_A: D13.2 (A), R69.2
/FT2/FT2_D_RXD: U8.52 (DDBUS1), U11.11
/FT2/FT2_D_RXI: R66.2, R67.2, U11.12
/FT2/FT2_D_TXD: U8.48 (DDBUS0), U11.5
/FT2/FT2_D_TXO: R65.1, U11.6
/FT2/FT2_EECLK: R45.2, U8.62 (EECLK), U9.4 (CLK)
/FT2/FT2_EECS: R44.2, U8.63 (EECS), U9.5 (CS)
/FT2/FT2_EEDATA: R47.2, U8.61 (EEDATA), U9.3 (DI)
/FT2/FT2_EE_DO: R46.2, R47.1, U9.1 (DO)
/FT2/FT2_OSCI: C38.1, U8.2 (OSCI), Y3.1
/FT2/FT2_OSCO: C39.1, U8.3 (OSCO), Y3.3
/FT2/FT2_REF: R48.1, U8.6 (REF)
/FT2/FT2_VPHY: C50.1, C51.1, FB3.2, U8.4 (VPHY)
/FT2/FT2_VPLL: C52.1, C53.1, FB4.2, U8.9 (VPLL)
FT2_DM: U8.7 (DM); also elsewhere on the board
FT2_DP: U8.8 (DP); also elsewhere on the board
FT2_RESET_N: R49.2, U8.14 (~RESET); also elsewhere on the board
GND: C37.2, C38.2, C39.2, C40.2, C41.2, C42.2, C43.2, C44.2, C45.2, C46.2, C47.2, C48.2, C49.2, C50.2, C51.2, C52.2, C53.2, C54.2, C55.2, D8.2 (GND), D11.2 (GND), J105.1, J106.1, J107.1, J108.1, R48.2, U8.1 (GND), U8.5 (GND), U8.10 (AGND), U8.11 (GND), U8.13 (TEST), U8.15 (GND), U8.25 (GND), U8.35 (GND), U8.47 (GND), U8.51 (GND), U9.2 (GND), U10.7 (GND), U10.10, U10.13, U11.7 (GND), U11.10, U11.13, Y3.2 (G), Y3.4 (G); also elsewhere on the board

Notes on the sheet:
FT4232H #2 -> CH05..CH08. EEPROM serial: SBCU-2 (program with ftdi_eeprom).
TX is driven only while DTR# is asserted (port open). LVC Ioff => Hi-Z when unpowered.
